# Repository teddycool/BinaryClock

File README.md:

# BinaryClock
A project to create a binary clock with a specially designed circuit-board and a raspberrypi zero

This project contains of several parts:
    * The circuitboard, made in Eagle CAD 
    * Raspberrypi code in python 2.7 written in PyCharm Community edition.
    * 3d models for a 3d-printed to the enclosure, made with tinkercad

Assembled and mounted in the 3d-printed enclosure:

The circuit board is a 'hat' to a raspberry pi zero with 20 WS2812B programmable LEDs for the clock-display, a 2x20 header
for the pi connection and some extra IOs and buttons. The board was manufactured by https://aisler.net that has a great quality service for small series of prototypes. 

The code depend on https://github.com/rpi-ws281x/rpi-ws281x-python Install this first.

It is a very simple 'game-loop' kind of program that updates every 1/5 second. Taking current time and  split to each figure (collumn) and then calculate  the bit-pattern and set the LEDs accordingly.

A simple user-manual and a technical description can be found in the project directory..

Future sw-improvements will add possibillities to configure colors and brightnes etc from outside.

Hardware version 3 is now ready and added a real-time clock directly on the circuitboard, some IOs to be controled by time, some extra buttons and a circuit for measuring the background light. 

Future hw-improvements will be to move the buttons to a better position when using the enclosure. 

Ref1: https://en.wikipedia.org/wiki/Binary_clock
Ref2: https://www.raspberrypi-spy.co.uk/2015/05/adding-a-ds3231-real-time-clock-to-the-raspberry-pi/

See pictures below for an other type of assembly with plexiglass as a 'sandwich'.

Pictures of hw version 1:

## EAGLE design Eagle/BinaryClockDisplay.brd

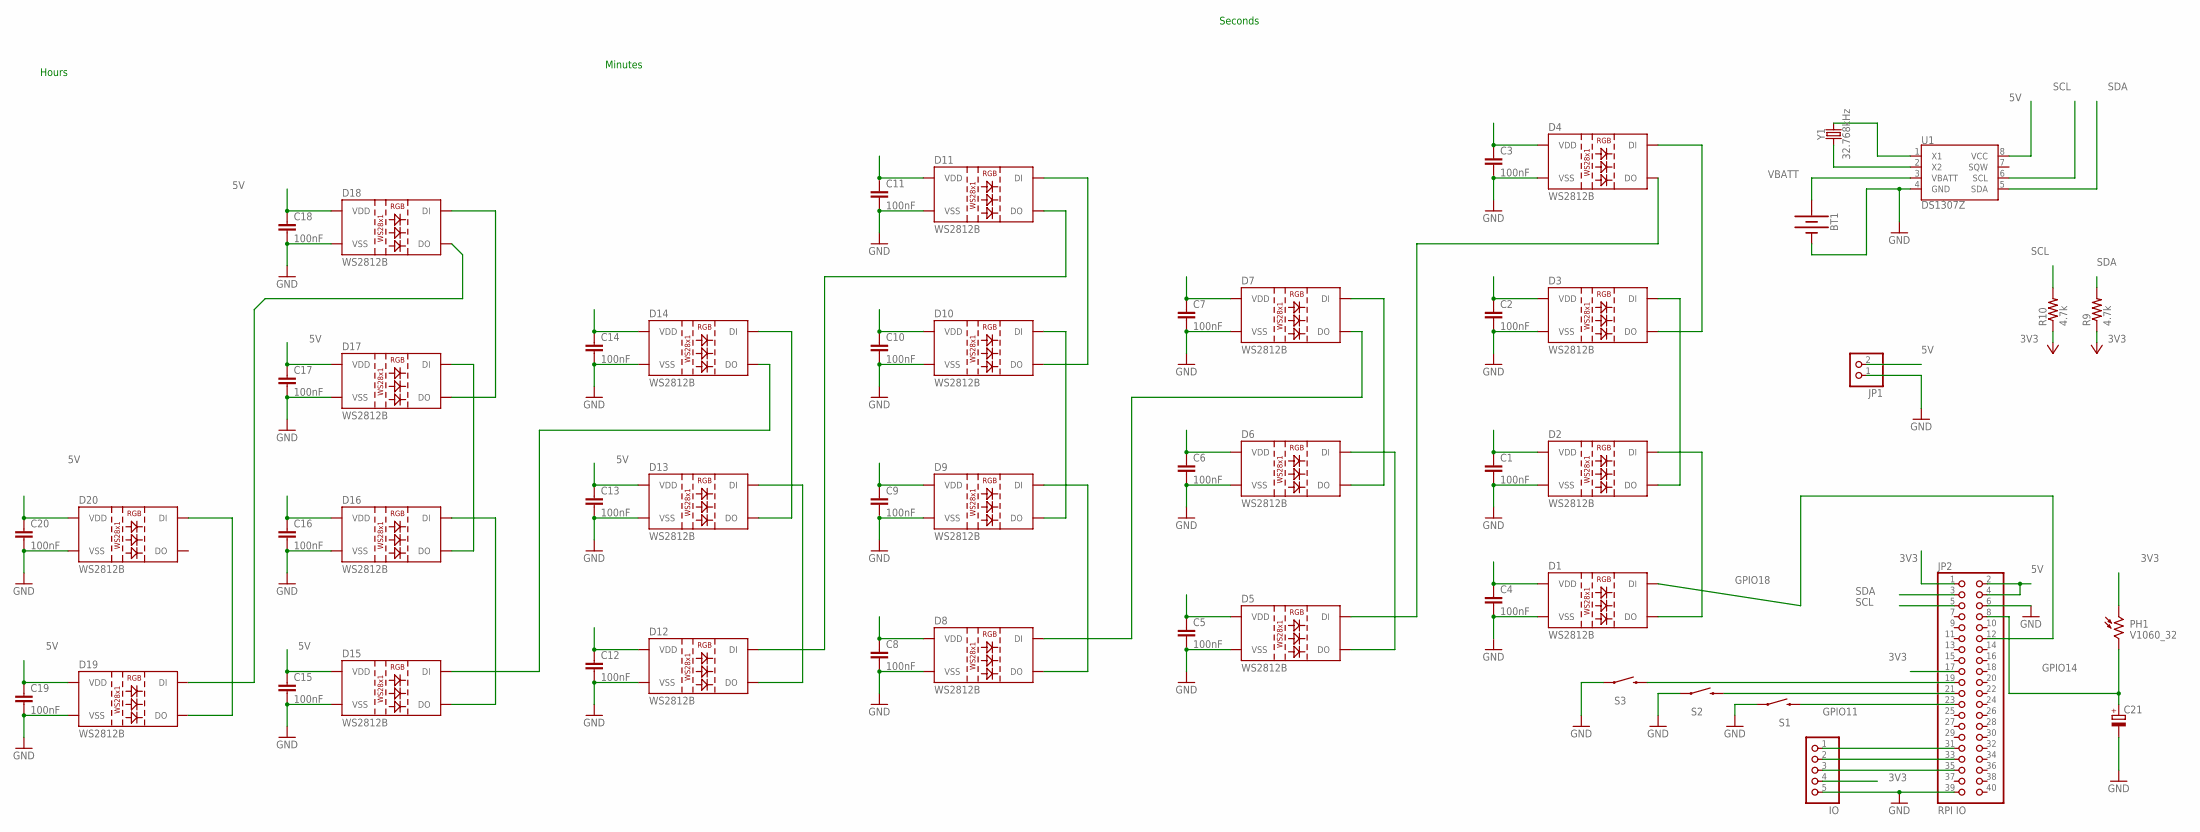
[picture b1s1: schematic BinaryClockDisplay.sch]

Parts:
BT1: BATTERY-20MM_PTH; BATTCOM_20MM_PTH
C1, C2, C3, C4, C5, C6, C7, C8, C9, C10, C11, C12, C13, C14, C15, C16, C17, C18, C19, C20: 100nF; 0805
C21: CPOL-EUE5-10.5; E5-10,5
D1, D2, D3, D4, D5, D6, D7, D8, D9, D10, D11, D12, D13, D14, D15, D16, D17, D18, D19, D20: WS2812B
JP1: PINHD-1X2; 1X02
JP2: RPI IO; 2X20
JP4: IO; 1X05
PH1: V1060_32; TO-5_V10
R9, R10: 4.7k; 0805
S1, S2, S3: SWITCH; TACTILE-SWITCH-1101NE
U1: DS1307Z; SO08-0.15
Y1: 32.768kHz; CRYSTAL-PTH-2X6-CYL

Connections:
3V3: JP2.1, JP2.17, JP4.4, PH1.1, R9.1, R10.1
5V: C1.1, C2.1, C3.1, C4.1, C5.1, C6.1, C7.1, C8.1, C9.1, C10.1, C11.1, C12.1, C13.1, C14.1, C15.1, C16.1, C17.1, C18.1, C19.1, C20.1, D1.1 (VDD), D2.1 (VDD), D3.1 (VDD), D4.1 (VDD), D5.1 (VDD), D6.1 (VDD), D7.1 (VDD), D8.1 (VDD), D9.1 (VDD), D10.1 (VDD), D11.1 (VDD), D12.1 (VDD), D13.1 (VDD), D14.1 (VDD), D15.1 (VDD), D16.1 (VDD), D17.1 (VDD), D18.1 (VDD), D19.1 (VDD), D20.1 (VDD), JP1.2, JP2.2, JP2.4, U1.8 (VCC)
GND: BT1.2 (-), C1.2, C2.2, C3.2, C4.2, C5.2, C6.2, C7.2, C8.2, C9.2, C10.2, C11.2, C12.2, C13.2, C14.2, C15.2, C16.2, C17.2, C18.2, C19.2, C20.2, C21.-, D1.3 (VSS), D2.3 (VSS), D3.3 (VSS), D4.3 (VSS), D5.3 (VSS), D6.3 (VSS), D7.3 (VSS), D8.3 (VSS), D9.3 (VSS), D10.3 (VSS), D11.3 (VSS), D12.3 (VSS), D13.3 (VSS), D14.3 (VSS), D15.3 (VSS), D16.3 (VSS), D17.3 (VSS), D18.3 (VSS), D19.3 (VSS), D20.3 (VSS), JP1.1, JP2.6, JP2.39, JP4.5, S1.1, S2.1, S3.1, U1.4 (GND)
GPIO6: JP2.31, JP4.1
GPIO9: JP2.21, S2.2
GPIO10: JP2.19, S3.2
GPIO11: JP2.23, S1.2
GPIO13: JP2.33, JP4.2
GPIO14: C21.+, JP2.8, PH1.2
GPIO18: D1.4 (DI), JP2.12
GPIO19: JP2.35, JP4.3
unnamed: D4.2 (DO), D5.4 (DI)
unnamed: D5.2 (DO), D6.4 (DI)
unnamed: D1.2 (DO), D2.4 (DI)
unnamed: D2.2 (DO), D3.4 (DI)
unnamed: D3.2 (DO), D4.4 (DI)
unnamed: U1.1 (X1), Y1.2
unnamed: D6.2 (DO), D7.4 (DI)
unnamed: D8.2 (DO), D9.4 (DI)
unnamed: D9.2 (DO), D10.4 (DI)
unnamed: D10.2 (DO), D11.4 (DI)
unnamed: D11.2 (DO), D12.4 (DI)
unnamed: D7.2 (DO), D8.4 (DI)
unnamed: D12.2 (DO), D13.4 (DI)
unnamed: D13.2 (DO), D14.4 (DI)
unnamed: D15.2 (DO), D16.4 (DI)
unnamed: D16.2 (DO), D17.4 (DI)
unnamed: D17.2 (DO), D18.4 (DI)
unnamed: D14.2 (DO), D15.4 (DI)
unnamed: U1.2 (X2), Y1.1
unnamed: D19.2 (DO), D20.4 (DI)
unnamed: D18.2 (DO), D19.4 (DI)
SCL: JP2.5, R10.2, U1.6 (SCL)
SDA: JP2.3, R9.2, U1.5 (SDA)
VBATT: BT1.1 (+), U1.3 (VBATT)

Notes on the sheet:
Hours
Minutes
Seconds

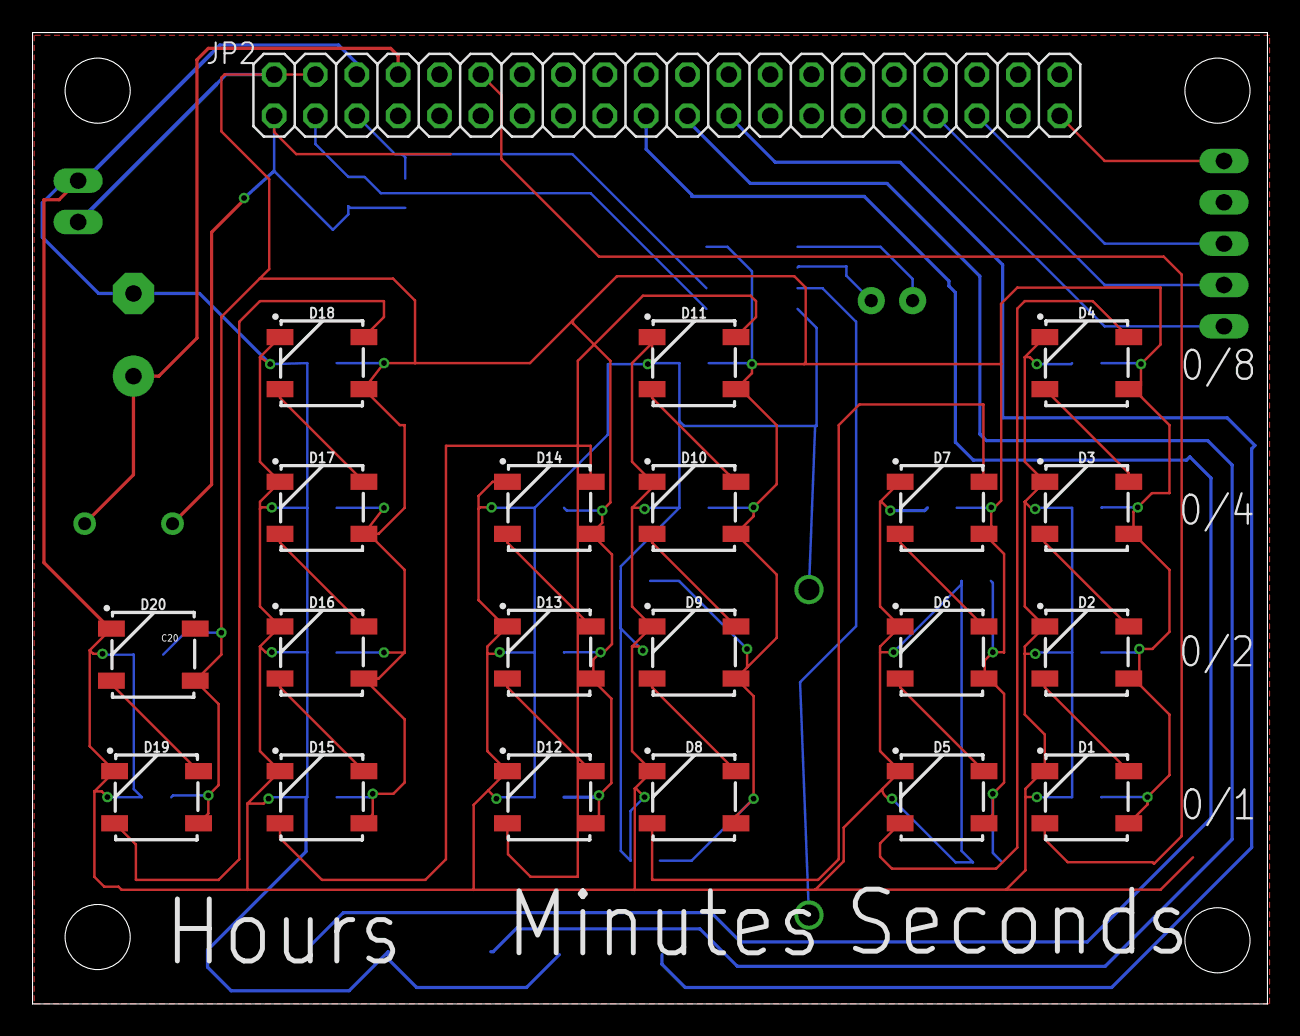
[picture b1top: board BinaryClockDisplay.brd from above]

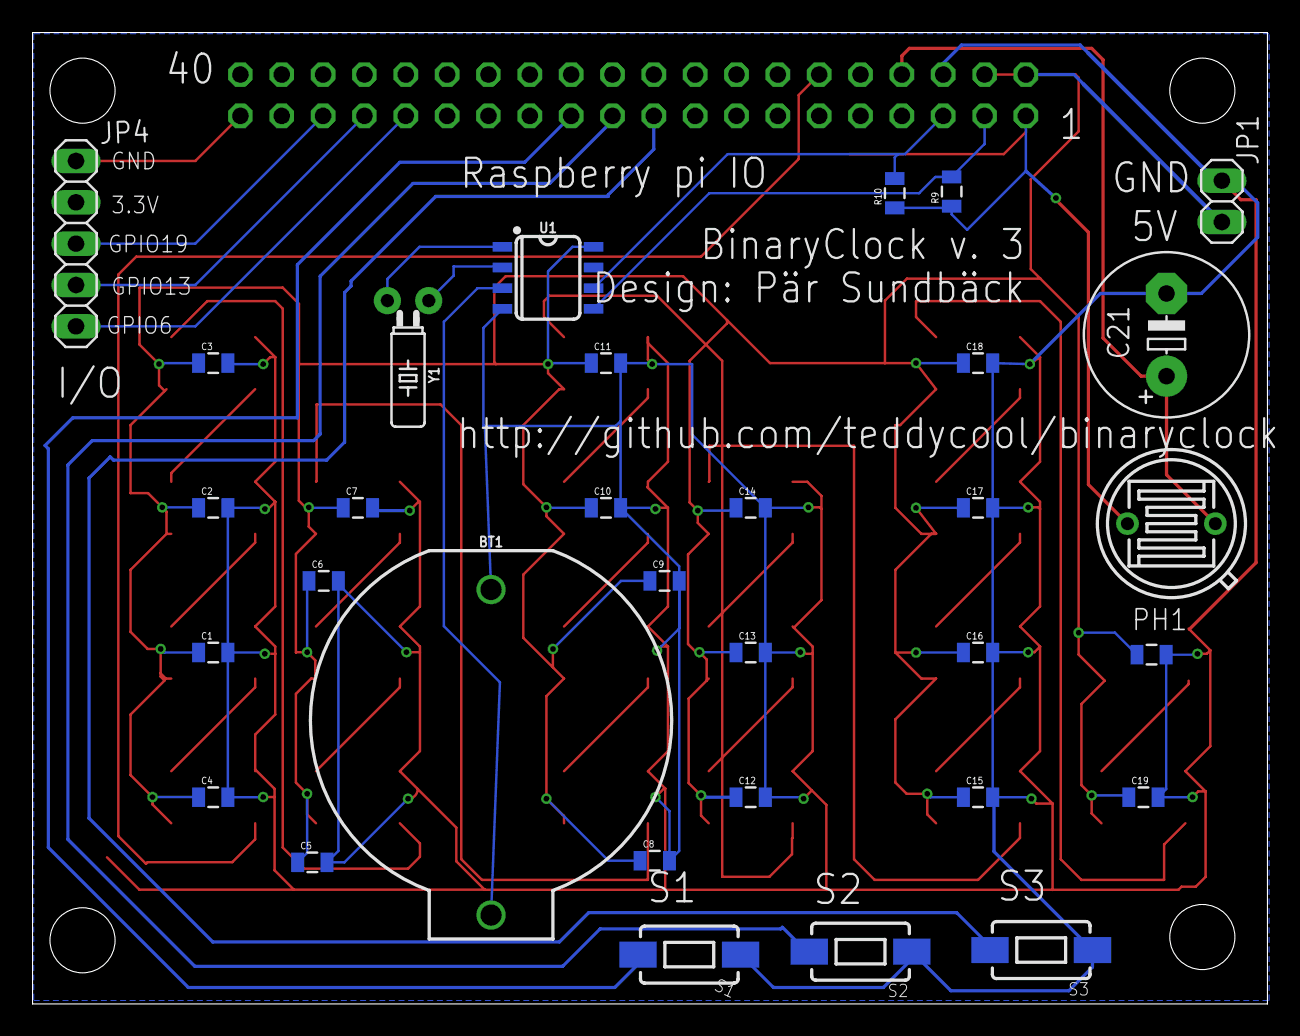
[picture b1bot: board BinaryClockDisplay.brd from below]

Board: 2 copper layers, 75.9 x 59.7 mm, 53 parts (32 on the bottom side), 35 nets.

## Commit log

2019-01-25 added files..
2019-01-26 Saturday morning work..
    Added python skeletton code
    Fixed RPi IO in circuit. Not tested...
2019-01-26 Updated circuit board
2019-01-27 Simplyfied design
    I decided to simmplify the design and make this a pure binary clock. Therefore I removed the interface to the 1602 display. I will look a bit cooler as binary only ;-)
2019-01-27 First version of complete board
2019-01-30 Adjusted schematics and circuit-board
2019-02-03 Circuitboard as ordered from Aisler 2019-02-03
    Also a
2019-02-11 First pictures
2019-02-15 Working code
    First version of code that shows the correct time.
2019-02-16 HW version 2
2019-02-16 Text added to version 2
2019-02-16 Fixed code
    See Main.py how to autostart the clock at power on
2019-02-16 Create PyBinaryClockHWv2
    Image of new version of PCB. Not yet tested!
2019-02-16 fixed image
2019-02-17 Cleaning out some unused files
2019-02-17 More fix and a temperature check turning off the pi if too hot
2019-02-18 Pictures on the real thing, version 1!
    This is it! Now it's done in a first version but I have allready more ideas for the future.
2019-02-19 HW version 2 allmost done...
2019-03-03 New version of hardware
    This is what I think is the final version #2 of the hardware with a real-time clock and some extra IO. It is NOT tested yet. Also some python changes but more will come when the hardware is ready.
2019-03-06 Circuitboard v.2 as ordered from Aisler
    The code for the new harware only partly updated
2019-03-22 Started working with sw for v 2
    A real state-machine and some structural changes.
2019-04-11 Working state machine
    Now with a working state-machine for clock-init, clock-loop and WiFi-setup. If not connected, the WPS setup is started and the pi is connected when the WPS push-button on the router ispressed.
    The brightness of the display is also set depending on background light.
2019-04-11 HW version 4
    Hardware version 4, not yet ordered. Only differnce from v 3 is the placement of the push-buttons.
2019-05-09 Added start for webconfig
2019-05-19 Documentation
    Updated the documentation and also added 3d printable modells for a first version of a cover.
2019-05-19 Documentation
2019-05-19 Create LICENSE
2019-05-21 Added new 3d-print models for enclosure

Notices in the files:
parts and their libraries:
SparkFun-LED: Licensing: Creative Commons ShareAlike 4.0 International - https://creativecommons.org/licenses/by-sa/4.0
